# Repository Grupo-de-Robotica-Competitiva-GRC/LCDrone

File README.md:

# Projeto drone STM32F103C8T6

Este é um projeto básico para demonstrar o uso do microcontrolador STM32F103C8T6.

## Descrição

O projeto utiliza o STM32CubeMX para configurar os pinos GPIO e gerar o código inicial para o STM32F103C8T6.

## Requisitos

- STM32CubeMX
- STM32CubeIDE ou ferramenta de desenvolvimento compatível com STM32

## Configuração

1. Abra o STM32CubeMX.
2. Carregue o arquivo de projeto (.ioc) fornecido neste repositório.
3. Verifique e ajuste a configuração dos pinos GPIO conforme necessário para o seu projeto.
4. Gere o código inicial e importe-o para a sua ferramenta de desenvolvimento.

## Compilação e Execução

1. Abra o projeto na STM32CubeIDE.
2. Compile o código.
3. Carregue o firmware gerado no microcontrolador STM32F103C8T6.

## Contribuições

Contribuições são bem-vindas via pull requests. Para mudanças importantes, por favor, abra uma issue primeiro para discutir o que você gostaria de mudar.

## Licença

Este projeto está licenciado sob a [Licença MIT]. Veja o arquivo LICENSE para mais detalhes.

---

### Configuração inicial do drone em STM32CubeMX (IOC):

---

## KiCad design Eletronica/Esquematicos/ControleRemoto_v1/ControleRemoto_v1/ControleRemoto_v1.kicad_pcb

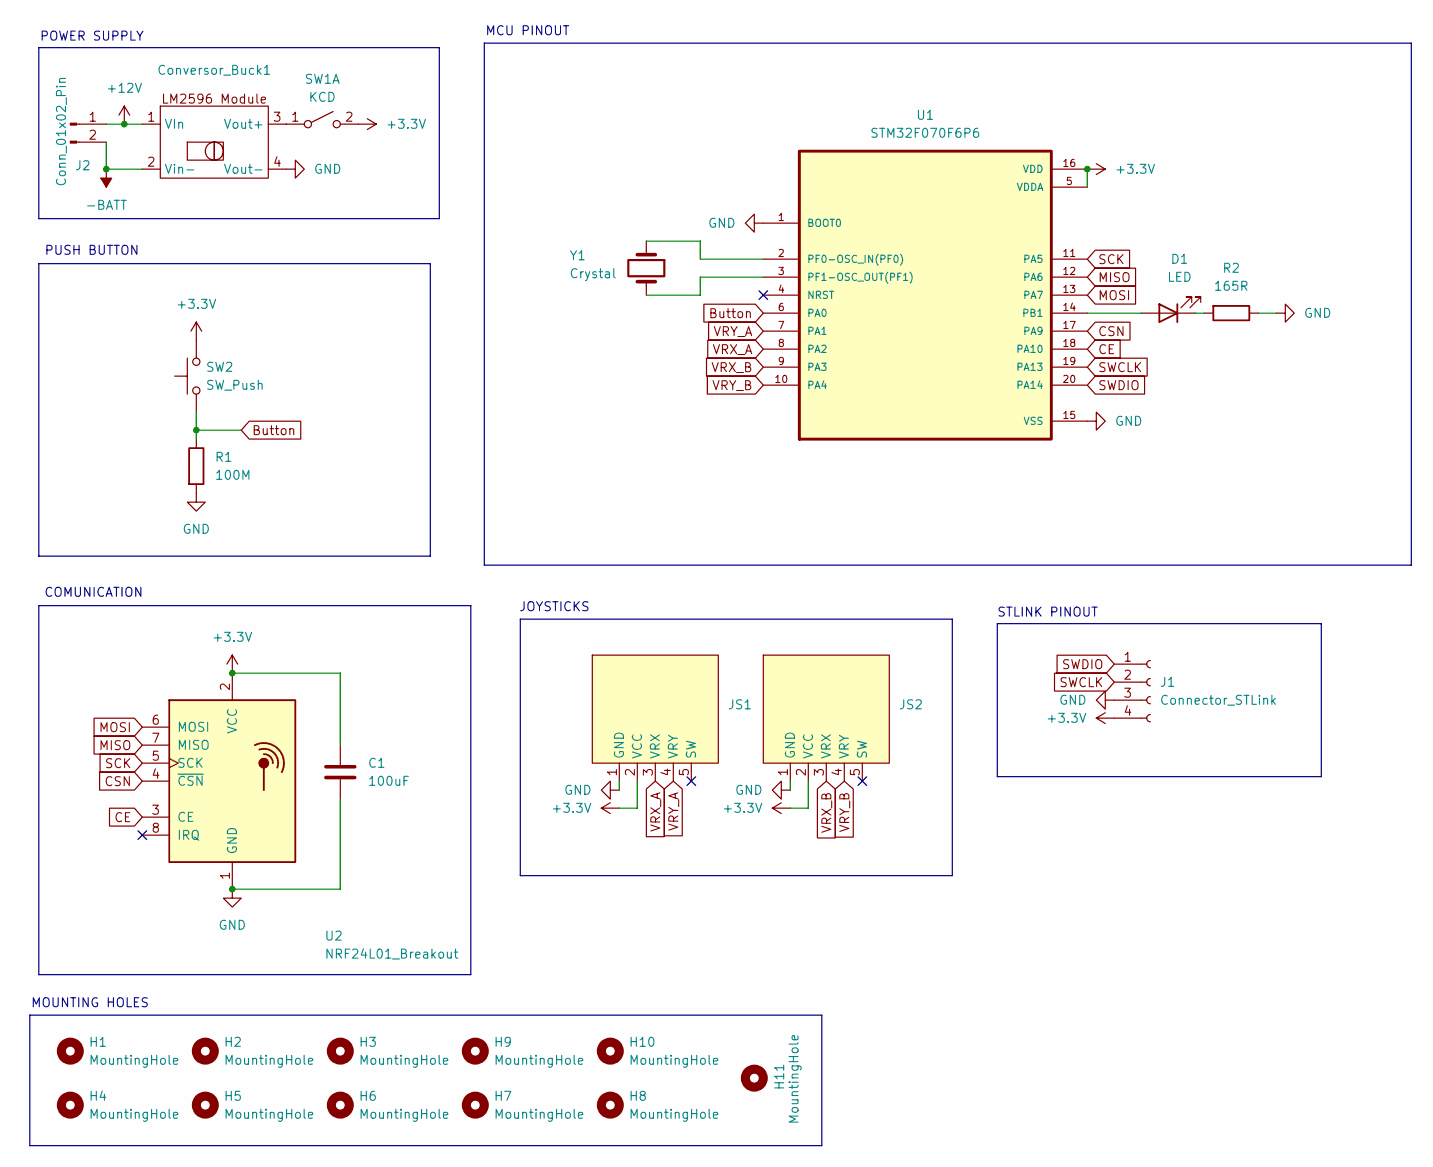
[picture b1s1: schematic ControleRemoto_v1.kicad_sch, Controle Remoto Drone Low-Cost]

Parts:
C1: 100uF; C_Disc_D3.0mm_W1.6mm_P2.50mm
Conversor_Buck1: YAAJ_DCDC_StepDown_LM2596
D1: LED; LED_D3.0mm_Clear
H1, H2, H3, H4, H5, H6, H7, H8, H9, H10, H11: MountingHole; MountingHole_2.5mm_Pad
J1: Connector_STLink; PinHeader_1x04_P2.54mm_Vertical
J2: Conn_01x02_Pin; PinHeader_1x02_P2.54mm_Vertical
JS1, JS2: PinSocket_1x05_P2.54mm_Vertical
R1: 100M; R_Axial_DIN0207_L6.3mm_D2.5mm_P7.62mm_Horizontal
R2: 165R; R_Axial_DIN0204_L3.6mm_D1.6mm_P5.08mm_Horizontal
SW1: KCD; sw_gangorra
SW2: SW_Push; SW_PUSH-12mm
U1: STM32F070F6P6; GREENPILL_STM32F070F6P6
U2: NRF24L01_Breakout; PinSocket_2x04_P2.54mm_Vertical
Y1: Crystal; Crystal_HC49-4H_Vertical

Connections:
+3.3V: C1.1, J1.4, JS1.2 (VCC), JS2.2 (VCC), SW1.2 (B), SW2.2, U1.5 (VDDA), U1.16 (VDD), U2.2 (VCC); also elsewhere on the board
+12V: Conversor_Buck1.1 (VIn), J2.1
-BATT: Conversor_Buck1.2 (Vin-), J2.2
Button: R1.1, SW2.1, U1.6 (PA0)
CE: U1.18 (PA10), U2.3 (CE)
CSN: U1.17 (PA9), U2.4 (~CSN)
GND: C1.2, Conversor_Buck1.4 (Vout-), J1.3, JS1.1 (GND), JS2.1 (GND), R1.2, R2.1, U1.1 (BOOT0), U1.15 (VSS), U2.1 (GND)
MISO: U1.12 (PA6), U2.7 (MISO)
MOSI: U1.13 (PA7), U2.6 (MOSI)
unnamed 9: Conversor_Buck1.3 (Vout+), SW1.1 (A); also elsewhere on the board
unnamed: D1.2 (A), U1.14 (PB1)
unnamed: D1.1 (K), R2.2
unnamed: U1.2 (PF0-OSC_IN(PF0)), Y1.1
unnamed: U1.3 (PF1-OSC_OUT(PF1)), Y1.2
SCK: U1.11 (PA5), U2.5 (SCK)
SWCLK: J1.2, U1.19 (PA13)
SWDIO: J1.1, U1.20 (PA14)
VRX_A: JS1.3 (VRX), U1.8 (PA2)
VRX_B: JS2.3 (VRX), U1.9 (PA3)
VRY_A: JS1.4 (VRY), U1.7 (PA1)
VRY_B: JS2.4 (VRY), U1.10 (PA4)

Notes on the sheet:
STLINK PINOUT
MOUNTING HOLES
PUSH BUTTON
COMUNICATION
JOYSTICKS
POWER SUPPLY
MCU PINOUT

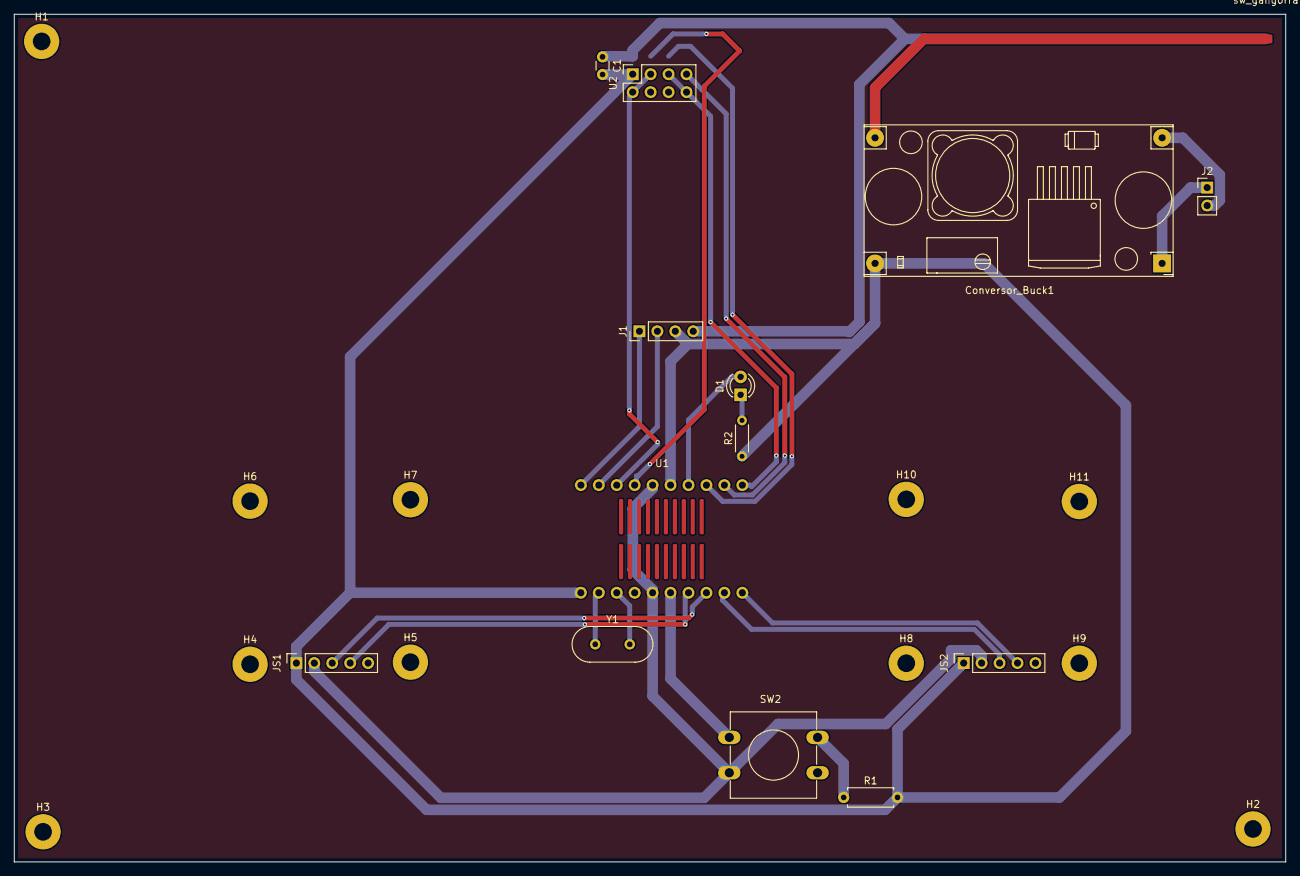
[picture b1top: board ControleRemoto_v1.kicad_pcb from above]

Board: 2 copper layers, 180.0 x 120.0 mm, 25 parts (0 on the bottom side), 21 nets.

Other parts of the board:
sw_gangorra: sw_gangorra

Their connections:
+3.3V: sw_gangorra.2; also elsewhere on the board
unnamed 9: sw_gangorra.1; also elsewhere on the board

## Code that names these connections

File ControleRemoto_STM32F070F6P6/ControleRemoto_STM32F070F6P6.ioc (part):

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Mcu.Name=STM32F070F6Px
Mcu.Package=TSSOP20
Mcu.UserName=STM32F070F6Px
PA0.Signal=GPIO_Input
PA1.Mode=IN1
PA1.Signal=ADC_IN1
PA10.GPIOParameters=GPIO_Label
PA10.GPIO_Label=CE
PA10.Signal=GPIO_Output
PA13.Mode=Serial_Wire
PA13.Signal=SYS_SWDIO
PA14.Mode=Serial_Wire
PA14.Signal=SYS_SWCLK
PA2.Mode=IN2
PA2.Signal=ADC_IN2
PA3.Mode=IN3
PA3.Signal=ADC_IN3
PA4.Mode=IN4
PA4.Signal=ADC_IN4
PA5.Mode=Full_Duplex_Master
PA5.Signal=SPI1_SCK
PA6.Mode=Full_Duplex_Master
PA6.Signal=SPI1_MISO
PA7.Mode=Full_Duplex_Master
PA7.Signal=SPI1_MOSI
PA9.GPIOParameters=GPIO_Label
PA9.GPIO_Label=CSN
PA9.Signal=GPIO_Output
PB1.GPIOParameters=GPIO_Label
PB1.GPIO_Label=LED
PB1.Signal=GPIO_Output
PF0-OSC_IN.Mode=HSE-External-Oscillator
PF0-OSC_IN.Signal=RCC_OSC_IN
PF1-OSC_OUT.Mode=HSE-External-Oscillator
PF1-OSC_OUT.Signal=RCC_OSC_OUT
RCC.HSE_VALUE=16000000
RCC.SYSCLKFreq_VALUE=48000000
RCC.SYSCLKSource=RCC_SYSCLKSOURCE_PLLCLK
board=custom

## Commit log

2024-07-01 configuracaoIOC
2024-07-01 projetoInicial
2024-07-01 configuração controle
2024-09-01 controle
2025-06-21 Add schematic pcb drone
2025-08-21 Organização de pastas em grupos de setor (Firmware, Eletronica, 3D e Testes)
2025-08-21 Codigo de teste do MPU utilizando registradores sem filtro de Kalman
2025-08-21 Imagens para o arquivo MuckDown
2025-08-21 Update MPU6050.md
    Finalização do MuckDown
2025-09-04 Código de teste do BMP180 adicionado a Testes
2025-09-08 Esquematico Novo
    Esquematico do Drone atualizado
2025-09-09 Adição do projeto do MPU com o filtro de Kalman aplicado e algumas organizações de pastas.
2025-09-09 Atualizar o main.c
2025-09-09 Adição do arquivo processing para visualização 3D controlada pelo MPU com filtro de Kalman
2025-09-11 Testes do NRF24L01
2025-09-11 Update NRF24L01 testes
2025-09-11 mudanças no controle grenn pill
2025-09-11 Atualização de Receptor para enviar via UART se foi recebido e o dado enviado, e tambem um arquivo do bmp180
2025-09-16 Arquivo do projeto
2025-09-17 Adicionado arquivos do esquemático novo
2025-12-21 Atualizar o MPU6050.md
